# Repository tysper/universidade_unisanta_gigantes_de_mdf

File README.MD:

# Gigantes de MDF - Trabalho de Programação de Hardware 2024 Unisanta

<div style="display:flex;flex-direction:column;justify-content:center;align-items:center;">
    
</div>

## Introdução

Este projeto integra os conhecimentos adquiridos na disciplina de Programação de Hardware do curso de Engenharia. Ele tem como objetivo principal o desenvolvimento de um robô funcional, com foco na programação do microcontrolador **ATMega328(p)(PB)**, utilizando periféricos como **PWM** e timers, além da implementação de um circuito eletrônico completo. A abordagem do projeto prioriza o aprendizado prático e evita o uso de soluções pré-prontas, garantindo que os participantes desenvolvam competências fundamentais na área.

## Objetivo do Projeto

Construir um robô funcional capaz de:
- Movimentar-se autonomamente utilizando motores controlados via PWM.
- Operar uma "arma laser" que dispara feixes de luz vermelha por 1 segundo, controlada por temporizadores.
- Detectar impactos de laser recebidos e reagir com ações programadas, como giros no eixo e decremento de LEDs que indicam "vidas".
- Integrar todos os componentes eletrônicos, incluindo sensores, LEDs e botões, em um circuito projetado manualmente.

## Requisitos Técnicos

### Mecânica
- Estrutura com dimensões máximas de **200x200x200 mm**.
- Sistema de movimentação em 4, 3 ou 2 rodas, permitindo rotações no próprio eixo.
- "Arma laser" centralizada e receptor de luz posicionado lateralmente.

Diagrama feito no autocad:

<i>Feito por <a href="https://github.com/tysper">Pedro Nunes</a></i>

### Eletrônica
- Circuitos para controle de motores projetados manualmente (sem shields prontos).
- Laser com potência máxima de **300 mW** e receptor de luz com difusor de 20 mm.
- LEDs indicativos para "vidas", com controle de estado por GPIO e um botão para reset.

<p>Circuito da placa principal desenvolvida para abrigar o microcontrolador ATMega328</p>

<br>
<p>Circuito da placa de ponte H</p>
</a><br />
<i>Feito por <a href="https://github.com/gabriele-siilva">Gabriele Silva</a></i>

### Programação
- Uso obrigatório de timers para controle do laser.
- Interrupções para funcionalidade do botão de reset.
- Controle dos motores baseado em PWM.
- Reação programada ao impacto de laser: desativação temporária do robô e decremento de LEDs.

<i>Feito por <a href="https://github.com/gabriele-siilva">Gabriele Silva</a>, <a href="https://github.com/tysper">Pedro Nunes</a>, <a href="https://github.com/arthursilles">Arthur Silles</a> e <a href="https://github.com/imyourmafe">Maria Fernanda</a>.</i>

## Estrutura de Desenvolvimento

###  1. Protótipo Funcional - 5 de outubro de 2024 ✅
O protótipo inicial do robô foi concluído, com movimentação básica utilizando os motores conectados a baterias. A estrutura mecânica foi montada conforme as especificações e demonstrada com sucesso.

###  2. Circuito Eletrônico e Funcionalidades Básicas - 31 de outubro de 2024 ✅
O circuito eletrônico foi projetado e integrado ao microcontrolador **ATMega328(p)(PB)**. Todas as funcionalidades básicas, incluindo controle dos motores, operação da "arma laser" e detecção do alvo foram implementadas, mas houveram alguns problemas que impediram a apresentação ao professor.

### 3. Apresentação Final - 23 de novembro de 2024 ✅
Apresentação concluída com sucesso. O video abaixo demonstra as funcionalidades básicas do projeto:

## Ferramentas e Requisitos Adicionais
- O código fonte foi desenvolvido exclusivamente, sem o uso de bibliotecas prontas, exceto aquelas previamente aprovadas pelo professor.
- A documentação do software foi elaborada utilizando a ferramenta **Doxygen**. E pode ser consultada no link: <a href="https://tysper.github.io/universidade_unisanta_gigantes_de_mdf/scripts/documentacao/html/index.html">Documentação - Gigantes de MDF</a>
- O repositório contém todos os arquivos do projeto, incluindo esquemas eletrônicos, código-fonte e documentação detalhada.

## Avaliação
O projeto foi avaliado com base nos seguintes critérios:
- Conformidade com os requisitos técnicos e funcionais.
- Qualidade e organização do código-fonte.
- Apresentação e documentação do projeto.

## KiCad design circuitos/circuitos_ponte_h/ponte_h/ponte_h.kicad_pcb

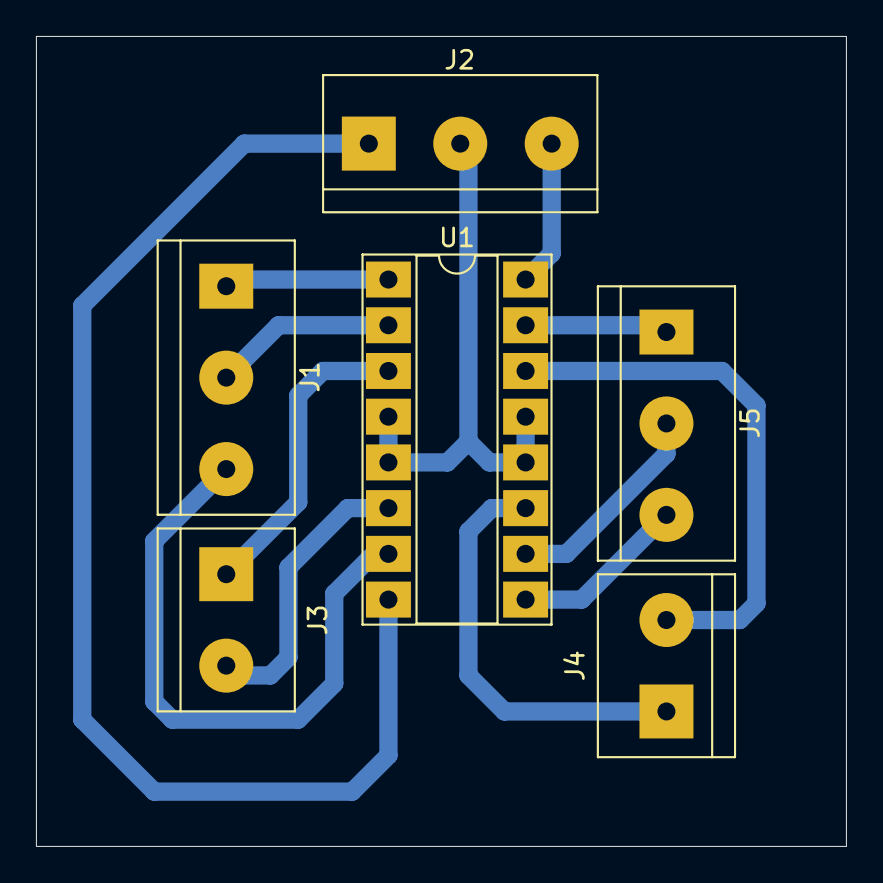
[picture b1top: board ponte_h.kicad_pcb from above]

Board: 2 copper layers, 45.0 x 45.0 mm, 6 parts (0 on the bottom side), 13 nets.

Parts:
J1, J5: Screw_Terminal_01x03; TerminalBlock_bornier-3_P5.08mm
J2: FONTE; TerminalBlock_bornier-3_P5.08mm
J3: MOTOR1; TerminalBlock_bornier-2_P5.08mm
J4: MOTOR2; TerminalBlock_bornier-2_P5.08mm
U1: L293D; DIP-16_W7.62mm_Socket_LongPads

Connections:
+5V: J2.3, U1.16 (VCC1)
+6V: J2.1, U1.8 (VCC2)
GND: J2.2, U1.4 (GND), U1.5 (GND), U1.12 (GND), U1.13 (GND)
IN1: J1.2, U1.2 (1A)
IN2: J1.3, U1.7 (2A)
IN3: J5.2, U1.10 (3A)
IN4: J5.1, U1.15 (4A)
unnamed: J3.1, U1.3 (1Y)
unnamed: J3.2, U1.6 (2Y)
unnamed: J4.1, U1.11 (3Y)
unnamed: J4.2, U1.14 (4Y)
PWM1: J1.1, U1.1 (EN1,2)
PWM2: J5.3, U1.9 (EN3,4)

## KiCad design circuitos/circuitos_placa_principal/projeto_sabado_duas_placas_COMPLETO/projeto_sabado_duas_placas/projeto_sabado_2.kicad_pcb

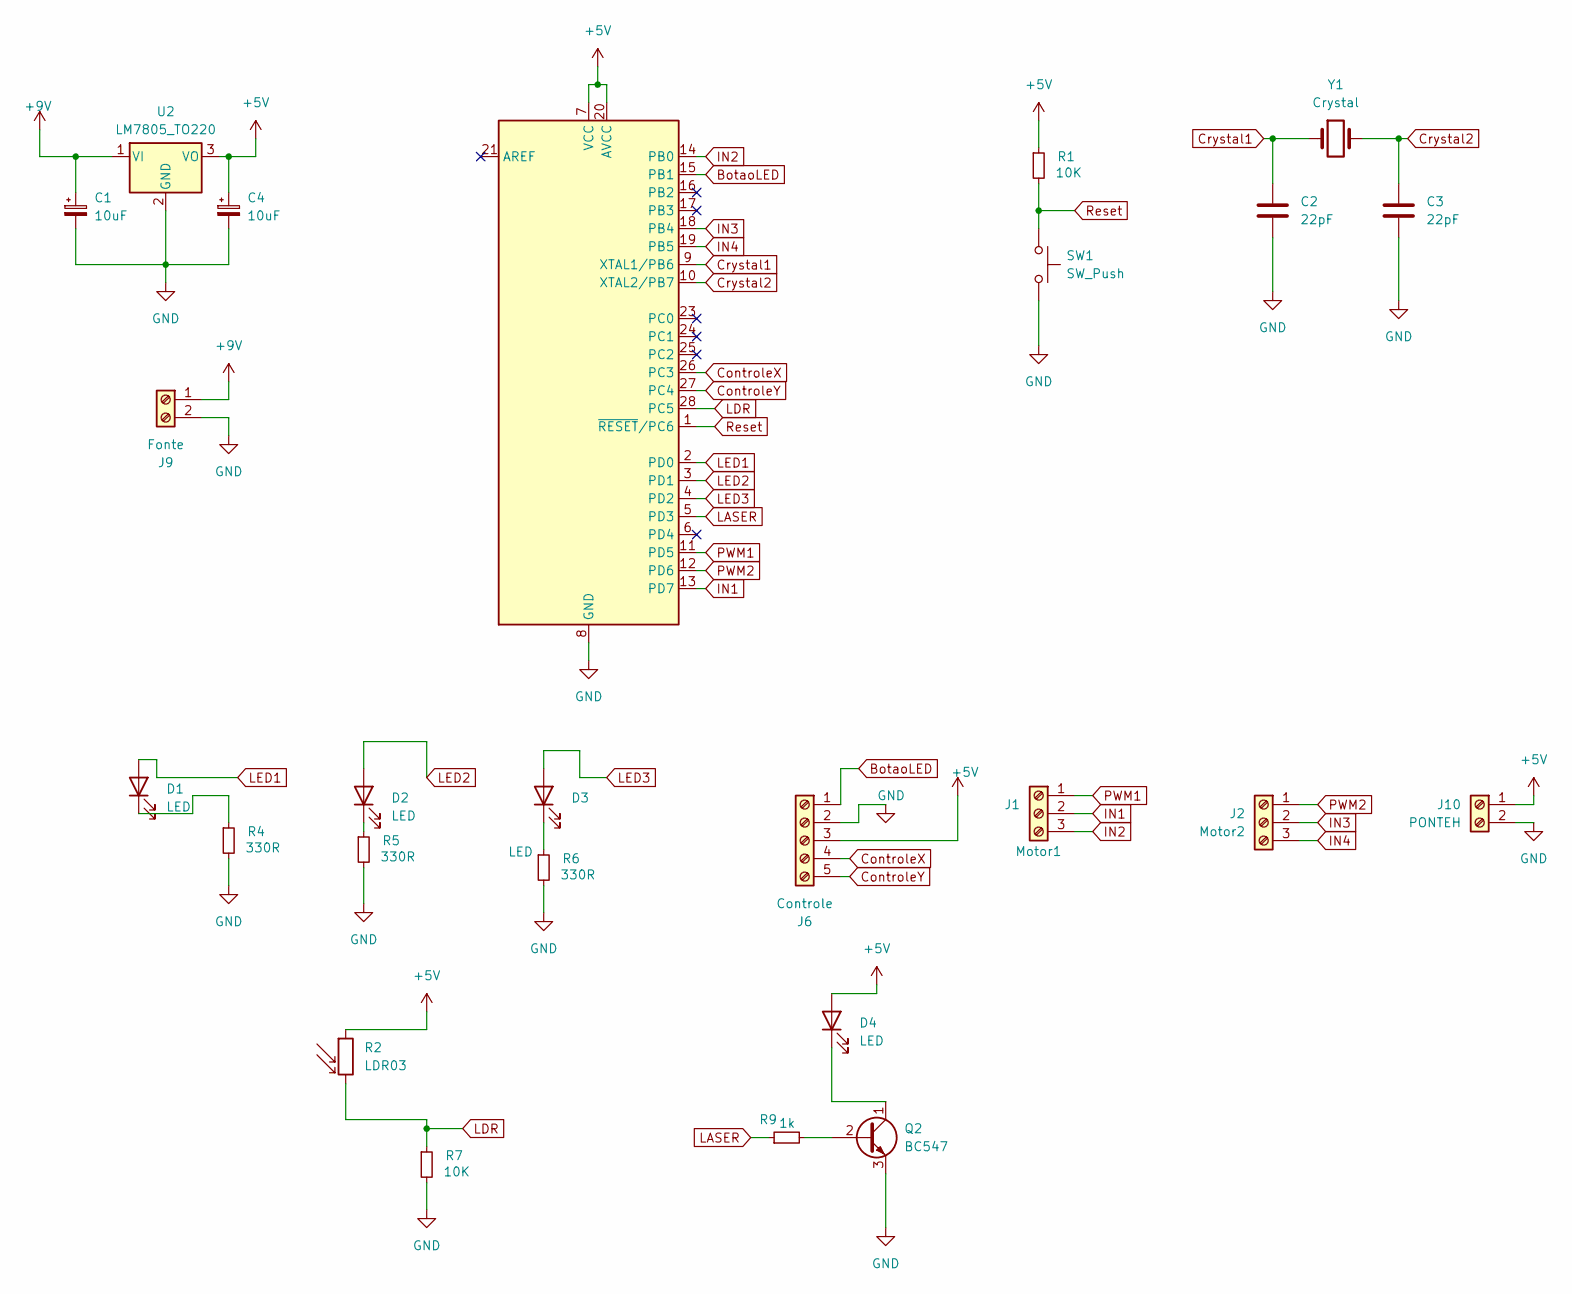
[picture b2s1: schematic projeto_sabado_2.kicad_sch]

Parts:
C1, C4: 10uF; CP_Radial_D8.0mm_P3.80mm
C2, C3: 22pF; C_Disc_D4.3mm_W1.9mm_P5.00mm
D1, D2, D3, D4: LED; LED_D3.0mm
J1: Motor1; TerminalBlock_bornier-3_P5.08mm
J2: Motor2; TerminalBlock_bornier-3_P5.08mm
J6: Controle; TerminalBlock_bornier-5_P5.08mm
J9: Fonte; TerminalBlock_bornier-2_P5.08mm
J10: PONTEH; TerminalBlock_bornier-2_P5.08mm
Q2: BC547; TO-92_Inline
R1, R7: 10K; R_Axial_DIN0207_L6.3mm_D2.5mm_P10.16mm_Horizontal
R2: LDR03; R_LDR_10x8.5mm_P7.6mm_Vertical
R4, R5, R6: 330R; R_Axial_DIN0207_L6.3mm_D2.5mm_P10.16mm_Horizontal
R9: 1k; R_Axial_DIN0207_L6.3mm_D2.5mm_P10.16mm_Horizontal
SW1: SW_Push; SW_PUSH_6mm_H5mm
U1: ATmega328P-P; DIP-28_W7.62mm_Socket
U2: LM7805_TO220; TO-220-3_Vertical
Y1: Crystal; Crystal_HC49-4H_Vertical

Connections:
+5V: C4.1, D4.2 (A), J6.3, J10.1, R1.1, R2.1, U1.7 (VCC), U1.20 (AVCC), U2.3 (VO)
+9V: C1.1, J9.1, U2.1 (VI)
BotaoLED: J6.1, U1.15 (PB1)
ControleX: J6.4, U1.26 (PC3)
ControleY: J6.5, U1.27 (PC4)
Crystal1: C2.1, U1.9 (XTAL1/PB6), Y1.1
Crystal2: C3.1, U1.10 (XTAL2/PB7), Y1.2
GND: C1.2, C2.2, C3.2, C4.2, J6.2, J9.2, J10.2, Q2.3 (E), R4.2, R5.2, R6.2, R7.2, SW1.2, U1.8 (GND), U1.22 (GND), U2.2 (GND)
IN1: J1.2, U1.13 (PD7)
IN2: J1.3, U1.14 (PB0)
IN3: J2.2, U1.18 (PB4)
IN4: J2.3, U1.19 (PB5)
LASER: R9.1, U1.5 (PD3)
LDR: R2.2, R7.1, U1.28 (PC5)
LED1: D1.2 (A), U1.2 (PD0)
LED2: D2.2 (A), U1.3 (PD1)
LED3: D3.2 (A), U1.4 (PD2)
unnamed: D1.1 (K), R4.1
unnamed: D2.1 (K), R5.1
unnamed: D3.1 (K), R6.1
unnamed: D4.1 (K), Q2.1 (C)
unnamed: Q2.2 (B), R9.2
PWM1: J1.1, U1.11 (PD5)
PWM2: J2.1, U1.12 (PD6)
Reset: R1.2, SW1.1, U1.1 (~RESET/PC6)

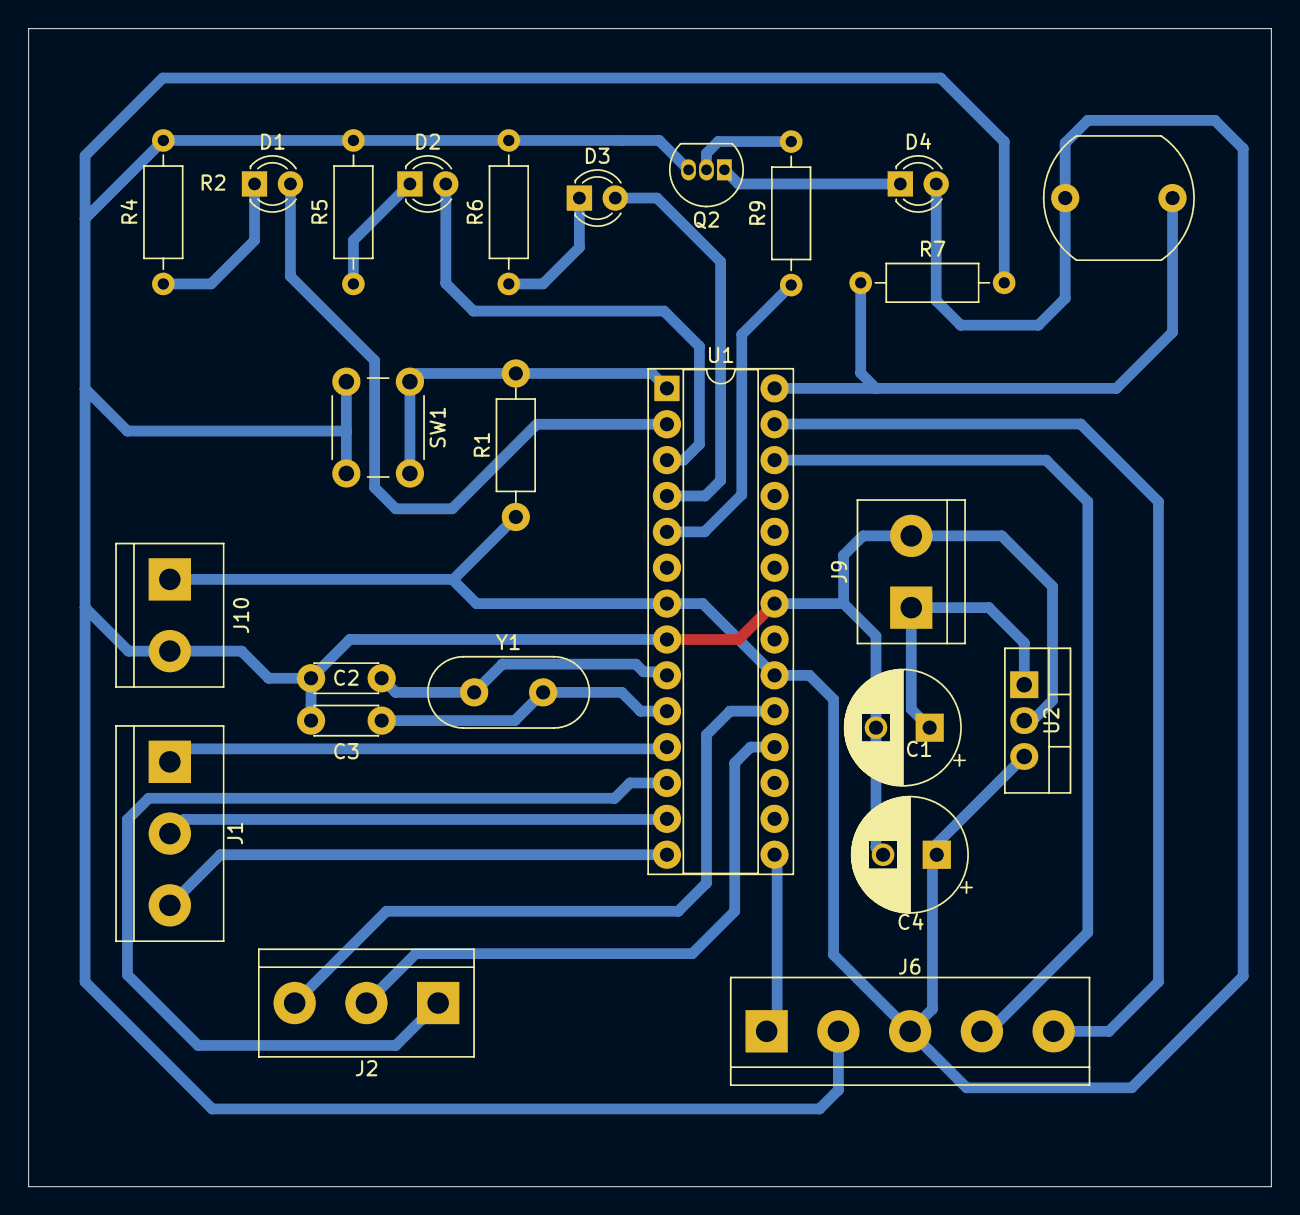
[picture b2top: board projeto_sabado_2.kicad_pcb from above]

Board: 2 copper layers, 88.0 x 82.0 mm, 25 parts (0 on the bottom side), 25 nets.

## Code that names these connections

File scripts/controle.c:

#include <avr/io.h>
#include <util/delay.h>
#include <avr/interrupt.h>

// Definições para os pinos PWM
#define PWM1_PIN PD5 // Motor 1 (OC0A)
#define PWM2_PIN PD6 // Motor 2 (OC0B)

// Definições de controle dos motores
#define MOTOR1_DIR1_PIN PD7 // Direção Motor 1
#define MOTOR1_DIR2_PIN PB0 // Direção Motor 1
#define MOTOR2_DIR1_PIN PB3 // Direção Motor 2
#define MOTOR2_DIR2_PIN PB4 // Direção Motor 2

// definições pinos LEDs, Botão e Laser
#define LED1 PD2
#define LED2 PD4
#define LED3 PB2
#define Laser PD3
#define BotaoLED PB5

// Prototipação de funções
void UART_init(uint16_t baud);
char UART_receive(void);
void PWM_init(void);
void motor_control(uint8_t motor, uint8_t direction, uint8_t speed);
int8_t map_joystick_value(uint8_t value);
void verificarSensor(void);
void atualizarVidas(void);
void girar180(void);

volatile uint8_t vidas = 3;        //Variável das vidas
volatile uint32_t ultimo_evento = 0; // Timestamp do último evento (para debounce)
volatile uint16_t total_ovf; // variável para contar os overflows para ligar o laser
void timer2_init_laser(void);
void ligaLED(void);
void pinosConfigurados(void);

int main(void)
{
    / Inicialização de UART e PWM
    UART_init(9600); // Comunicação serial com baudrate 9600
    PWM_init();      // Inicializa os PWMs

    // Configuração dos pinos de direção dos motores como saída
    DDRB |= (1 << MOTOR1_DIR1_PIN) | (1 << MOTOR1_DIR2_PIN) | (1 << MOTOR2_DIR1_PIN) | (1 << MOTOR2_DIR2_PIN);

    // Configuração inicial dos motores
    motor_control(1, 0, 0); // Motor 1 parado
    motor_control(2, 0, 0); // Motor 2 parado

    // Configuração de interrupção externa para o sensor
    EICRA |= (1 << ISC01); // Interrupção em borda de descida
    EIMSK |= (1 << INT0);  // Habilita INT0
    sei();                 // Habilita interrupções globais

    uint8_t joystick_x = 127; // Posição neutra no eixo X
    uint8_t joystick_y = 127; // Posição neutra no eixo Y

    // Funções para controle dos pinos e timer que controla o laser
    pinosConfigurados();
    timer2_init_laser();
    sei(); // habilita interrupções globais

    while (1)
    {
        // Verifica o sensor de laser
        verificarSensor();

        // Controle do joystick existente
        joystick_x = UART_receive();
        joystick_y = UART_receive();

        int8_t x_mapped = map_joystick_value(joystick_x);
        int8_t y_mapped = map_joystick_value(joystick_y);

        int8_t motor1_speed = y_mapped + x_mapped;
        int8_t motor2_speed = y_mapped - x_mapped;

        uint8_t motor1_pwm = (motor1_speed > 0) ? motor1_speed : -motor1_speed;
        uint8_t motor2_pwm = (motor2_speed > 0) ? motor2_speed : -motor2_speed;

        motor_control(1, (motor1_speed >= 0) ? 1 : 2, motor1_pwm);
        motor_control(2, (motor2_speed >= 0) ? 1 : 2, motor2_pwm);
    }
    return 0;
}

// Inicialização da UART
void UART_init(uint16_t baud)
{
    uint16_t ubrr = F_CPU / 16 / baud - 1;  // Calcula o valor para UBRR
    UBRR0H = (ubrr >> 8);                   // Configuração do baud rate (parte alta)
    UBRR0L = ubrr;                          // Configuração do baud rate (parte baixa)
    UCSR0B = (1 << RXEN0) | (1 << TXEN0);   // Habilita RX e TX
    UCSR0C = (1 << UCSZ01) | (1 << UCSZ00); // Modo assíncrono, 8 bits de dados, 1 stop bit
}

// Recepção de um caractere pela UART
char UART_receive(void)
{
    while (!(UCSR0A & (1 << RXC0))); // Aguarda até receber o dado
    return UDR0; // Retorna o dado recebido
}

// Inicialização do PWM para controle dos motores
void PWM_init()
{
    // Configura os pinos PD6 (OC0A) e PD5 (OC0B) como saída
    DDRD |= (1 << PD6) | (1 << PD5);

    // Configura o Timer/Counter0 no modo Fast PWM
    // Modo Fast PWM: WGM02 = 0, WGM01 = 1, WGM00 = 1
    TCCR0A |= (1 << WGM01) | (1 << WGM00);
    TCCR0B &= ~(1 << WGM02);

    // Habilita a saída PWM em OC0A (PD6) e OC0B (PD5)
    // Configura o modo Clear on Compare Match
    TCCR0A |= (1 << COM0A1) | (1 << COM0B1); // Saídas PD6 e PD5

    // Configura o prescaler para 8 (frequência adequada para PWM em motores)
    TCCR0B |= (1 << CS01);
    TCCR0B &= ~((1 << CS02) | (1 << CS00));

    // Inicializa os valores dos PWMs com duty cycle 0
    OCR0A = 0; // Motor 1
    OCR0B = 0; // Motor 2
}

// Controle dos motores
void motor_control(uint8_t motor, uint8_t direction, uint8_t speed)
{
    if (motor == 1)
    { // Motor 1
        if (direction == 1)
        { // Para frente
            PORTB |= (1 << MOTOR1_DIR1_PIN);
            PORTB &= ~(1 << MOTOR1_DIR2_PIN);
        }
        else if (direction == 2)
        { // Para trás
            PORTB |= (1 << MOTOR1_DIR2_PIN);
            PORTB &= ~(1 << MOTOR1_DIR1_PIN);
        }
        else
        { // Parado
            PORTB &= ~((1 << MOTOR1_DIR1_PIN) | (1 << MOTOR1_DIR2_PIN));
        }
        OCR0B = speed; // Ajusta o PWM do Motor 1
    }
    else if (motor == 2)
    { // Motor 2
        if (direction == 1)
        { // Para frente
            PORTB |= (1 << MOTOR2_DIR1_PIN);
            PORTB &= ~(1 << MOTOR2_DIR2_PIN);
        }
        else if (direction == 2)
        { // Para trás
            PORTB |= (1 << MOTOR2_DIR2_PIN);
            PORTB &= ~(1 << MOTOR2_DIR1_PIN);
        }
        else
        { // Parado
            PORTB &= ~((1 << MOTOR2_DIR1_PIN) | (1 << MOTOR2_DIR2_PIN));
        }
        OCR0A = speed; // Ajusta o PWM do Motor 2
    }
}

// Mapeia o valor do joystick de 0-255 para -100 a +100
int8_t map_joystick_value(uint8_t value)
{
    return ((int16_t)value - 127) * 100 / 127;
}

// Função que controla o Laser
void timer2_init_laser()
{
    // prescale de 1024
    TCCR2B |= (1 << CS21) | (1 << CS22) | (1 << CS20);
    TCNT2 = 0;
    TIMSK2 |= (1 << TOIE2);
    total_ovf = 0;
}
ISR(TIMER2_OVF_vect)
{
    total_ovf++;
    // 16Mhz/1024=15625 -> 1/15625 = 64us-> 255*64us = 16,32ms -> 1/16,32ms = 61
    if (total_ovf >= 61)
    {
        PORTD ^= (1 << Laser);
        total_ovf = 0;
    }
}
void ligaLED()
{
    PORTD |= (1 << LED1) | (1 << LED2);
    PORTB |= (1 << LED3);
}
void pinosConfigurados()
{
    DDRB |= (1 << LED3);
    DDRD |= (1 << LED1) | (1 << LED2) | (1 << Laser);
    // habilitar pull up do botao
    PORTB |= (1 << PB5);
    // configuracao da interrupção do botao
    PCICR |= (1 << PCIE0);   // registrador PORTB
    PCMSK0 |= (1 << PCINT5); // pino PB5
}
ISR(PCINT0_vect)
{
    if (!(PINB & (1 << BotaoLED)))
    {
        ligaLED();
    }
}

void verificarSensor(void)
{
    if (!(PIND & (1 << PD3)))
    {
        uint32_t tempo_atual = millis(); // Função fictícia para o exemplo
        if (tempo_atual - ultimo_evento > 200) // Debounce de 200ms
        {
            ultimo_evento = tempo_atual;
            atualizarVidas();
        }
    }
}

void atualizarVidas(void)
{
    if (vidas > 0)
    {
        if (vidas > 0)
        {
        if (vidas == 3)
        {
            PORTB &= ~(1 << LED3); // Apaga o LED3
        }
        else if (vidas == 2)
        {
            PORTD &= ~(1 << LED2); // Apaga o LED2
        }
        else if (vidas == 1)
        {
            PORTD &= ~(1 << LED1); // Apaga o LED1
        }
        vidas--; // Reduz uma vida
        girar180(); // Faz o robô girar 180°
    }
}

void girar180(void)
{
    for (uint8_t i = 0; i < 5; i++) // Pequenos giros em 5 etapas
    {
        motor_control(1, 1, 255); // Motor 1 para frente
        motor_control(2, 2, 255); // Motor 2 para trás
        _delay_ms(200); // Pequenos intervalos de movimento
    }
    motor_control(1, 0, 0); // Para motor 1
    motor_control(2, 0, 0); // Para motor 2
}

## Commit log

2024-11-19 Commit inicial - implementação da comunicacao serial, controle dos motores e led
2024-11-19 Adiciona as funções de controle para o laser e botão de reset
2024-11-22 Correção das portas dos motores
2024-11-22 Correção OCR0A e OCR0B invertidos
2024-11-22 controle.c
2024-11-22 Correção da função de vidas e giro
2024-11-23 Código Finalizado
2024-11-23 Finalização do readme.md
2024-11-23 Correções de traduções
2024-11-29 Arquivos adicionais
